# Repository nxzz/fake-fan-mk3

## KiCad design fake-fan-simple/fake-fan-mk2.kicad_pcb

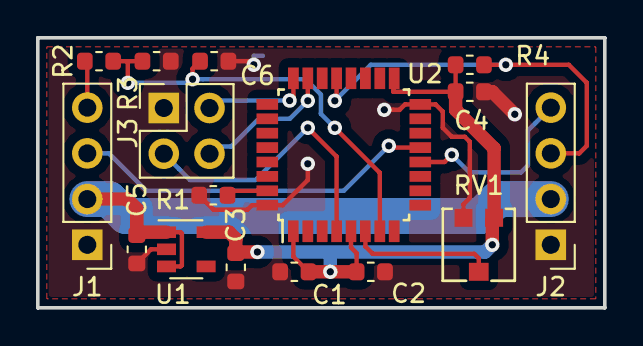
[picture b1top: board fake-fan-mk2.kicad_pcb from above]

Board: 2 copper layers, 31.5 x 15.0 mm, 16 parts (0 on the bottom side), 13 nets.

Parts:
C1: 0.47u; C_0603_1608Metric
C2, C3, C4, C5, C6: 0.1u; C_0603_1608Metric
J1: FIN1; PinHeader_1x04_P2.54mm_Vertical
J2: FOUT1; PinHeader_1x04_P2.54mm_Vertical
J3: SWD; PinHeader_2x02_P2.54mm_Vertical
R1: 10k; R_0603_1608Metric
R2, R3, R4: 22k; R_0603_1608Metric
RV1: 22k; PVZ3A
U1: NJM12888; SOT-23-5
U2: STM32F030K6Tx; LQFP-32_7x7mm_P0.8mm

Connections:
+3V3: C1.2, C2.2, C3.2, C4.2, R4.2, RV1.1, U1.5, U2.1, U2.5, U2.17
+12V: C5.2, J1.2, J2.2, U1.1, U1.3
/FAKE_PULSE: J1.3, U2.13
/FAN_PULSE: J2.3, R4.1, U2.21
/FAN_PWM: J2.4, U2.12
/NRST: J3.3, U2.4
/PWMIN: J1.4, R2.2
/PWMIN_3V: C6.2, R2.1, R3.2, U2.7
/SWDIO: J3.4, U2.23
/SYS_CLK: J3.2, U2.24
/VR1: RV1.2, U2.6
GND: C1.1, C2.1, C3.1, C4.1, C5.1, C6.1, J1.1, J2.1, J3.1, R1.2, R3.1, RV1.3, U1.2, U2.16, U2.32
unnamed: R1.1, U2.31

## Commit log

2020-07-31 kicad プロジェクトを追加
2020-09-02 ADCを追加 TIMのパラメータを再設定
2020-09-02 新版基板
2020-09-02 vscodeのコンフィグ追加 整理
2020-09-03 Fanの回転以上を本体側に通知するように
2020-09-11 回路更新
